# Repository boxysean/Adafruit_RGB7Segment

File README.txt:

This is a library for the Adafruit RGB 7 Segment with TLC5947 breakout board

Written by Sean McIntyre.
MIT license, all text above must be included in any redistribution

Place the Adafruit_RGB7Segment library folder your <arduinosketchfolder>/libraries/ folder. You may need to create the libraries subfolder if its your first library. Restart the IDE

**** Also requires the Tlc5940 library for Arduino. ****
Download it from here:
	https://code.google.com/p/tlc5940arduino/

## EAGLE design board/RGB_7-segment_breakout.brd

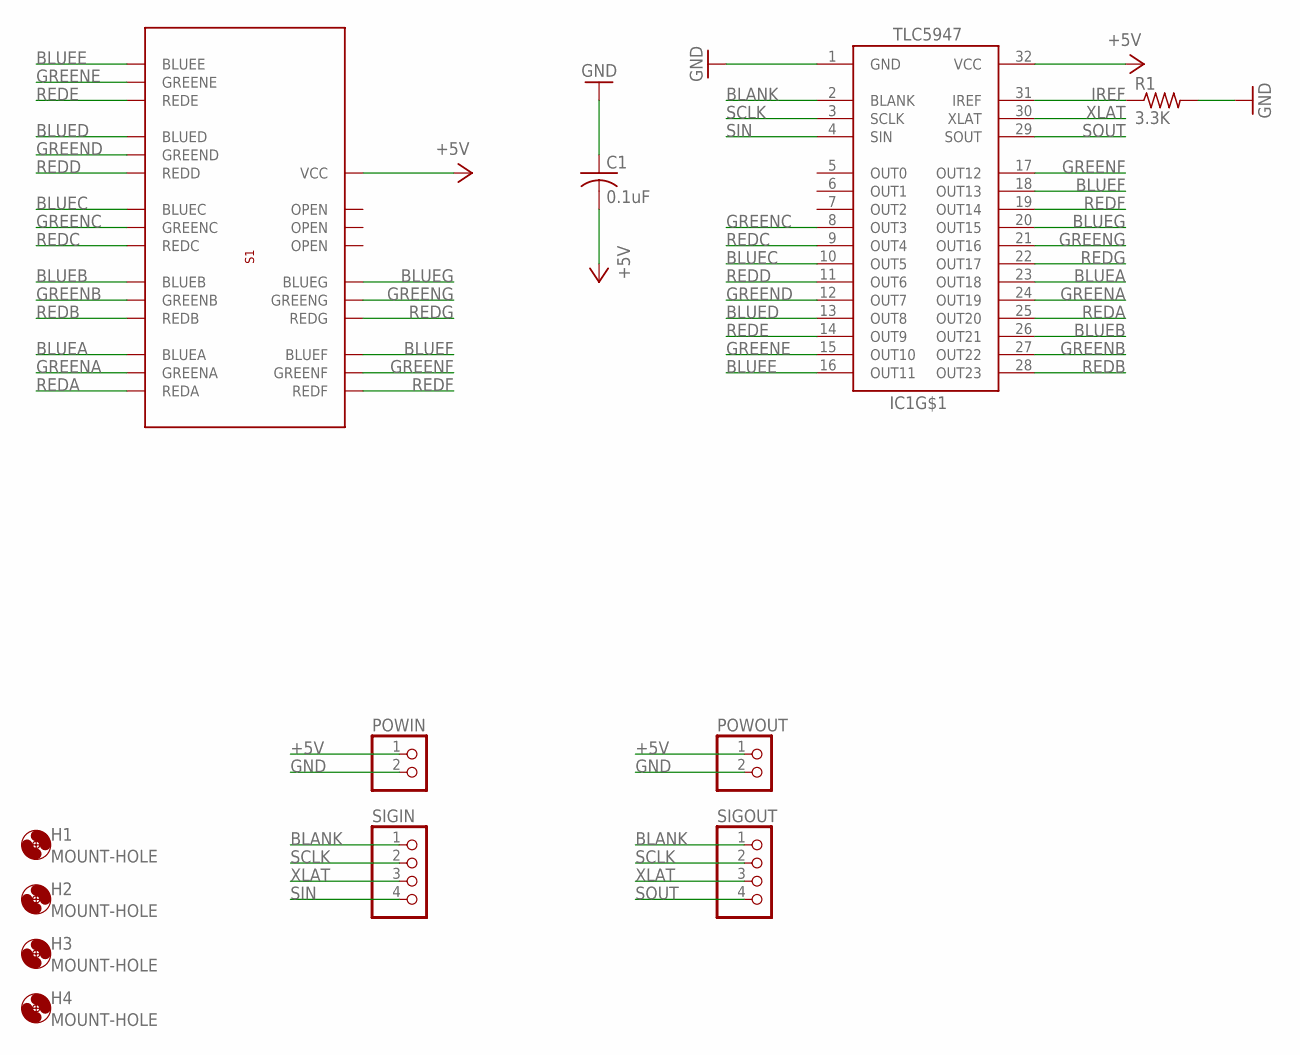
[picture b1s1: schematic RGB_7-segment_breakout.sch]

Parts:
C1: 0.1uF; C025-025X050
H1, H2, H3, H4: MOUNT-HOLE; 2,1
IC1: TLC5947-DAP; HTSSOP32DAP
POWIN: PINHD-1X2; 1X02
POWOUT: PINHD-1X2; 1X02
R1: 3.3K; 0207/10
S1: AD-121F2
SIGIN: PINHD-1X4; 1X04
SIGOUT: PINHD-1X4; 1X04

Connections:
+5V: C1.2, IC1.32 (VCC), POWIN.1, POWOUT.1, S1.P$17 (VCC)
BLANK: IC1.2 (BLANK), SIGIN.1, SIGOUT.1
BLUEA: IC1.23 (OUT18), S1.P$21 (BLUEA)
BLUEB: IC1.26 (OUT21), S1.P$24 (BLUEB)
BLUEC: IC1.10 (OUT5), S1.P$5 (BLUEC)
BLUED: IC1.13 (OUT8), S1.P$2 (BLUED)
BLUEE: IC1.16 (OUT11), S1.P$9 (BLUEE)
BLUEF: IC1.18 (OUT13), S1.P$18 (BLUEF)
BLUEG: IC1.20 (OUT15), S1.P$19 (BLUEG)
GND: C1.1, IC1.1 (GND), POWIN.2, POWOUT.2, R1.2
GREENA: IC1.24 (OUT19), S1.P$22 (GREENA)
GREENB: IC1.27 (OUT22), S1.P$16 (GREENB)
GREENC: IC1.8 (OUT3), S1.P$11 (GREENC)
GREEND: IC1.12 (OUT7), S1.P$3 (GREEND)
GREENE: IC1.15 (OUT10), S1.P$1 (GREENE)
GREENF: IC1.17 (OUT12), S1.P$13 (GREENF)
GREENG: IC1.21 (OUT16), S1.P$15 (GREENG)
IREF: IC1.31 (IREF), R1.1
REDA: IC1.25 (OUT20), S1.P$23 (REDA)
REDB: IC1.28 (OUT23), S1.P$25 (REDB)
REDC: IC1.9 (OUT4), S1.P$6 (REDC)
REDD: IC1.11 (OUT6), S1.P$4 (REDD)
REDE: IC1.14 (OUT9), S1.P$10 (REDE)
REDF: IC1.19 (OUT14), S1.P$14 (REDF)
REDG: IC1.22 (OUT17), S1.P$20 (REDG)
SCLK: IC1.3 (SCLK), SIGIN.2, SIGOUT.2
SIN: IC1.4 (SIN), SIGIN.4
SOUT: IC1.29 (SOUT), SIGOUT.4
XLAT: IC1.30 (XLAT), SIGIN.3, SIGOUT.3

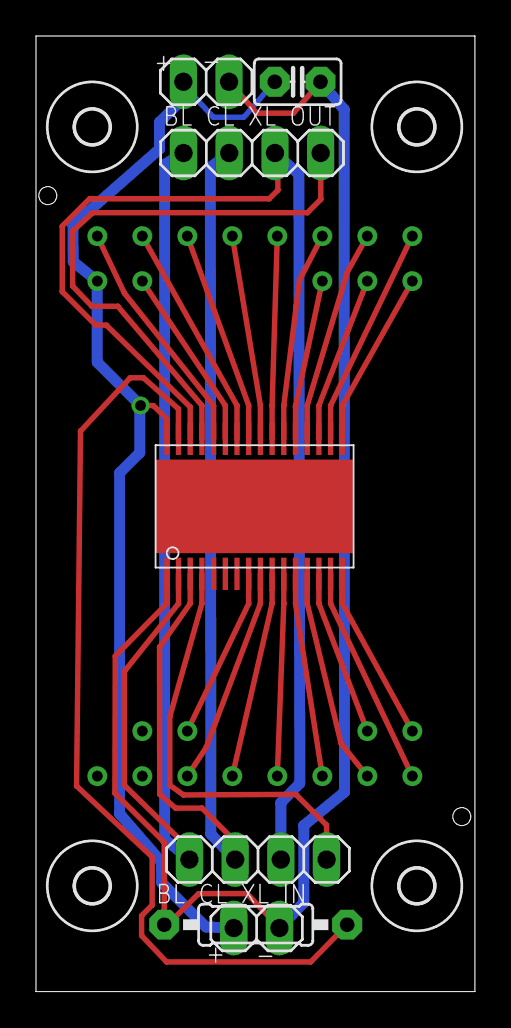
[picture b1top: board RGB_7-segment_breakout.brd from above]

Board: 2 copper layers, 24.4 x 53.1 mm, 12 parts (1 on the bottom side), 29 nets.

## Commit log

2014-08-14 added pin schematic
2014-08-25 added Arduino lib
2014-08-25 Revert "added Arduino lib"
    This reverts commit 95c9ae2c9446c8e4f55a4d97a93afe939340cbfc.
